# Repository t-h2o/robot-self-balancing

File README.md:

# robot-self-balancing

A self balancing robot made in [ETML](https://www.etml.ch/formations/automaticien.html)
was the final project of my CFC formation as automatician.

## PCB

The pcb has been designed with [KiCad](https://en.wikipedia.org/wiki/KiCad).
A very nice open-source software !

### Schematic

<p align="middle">
</p>

### PCB

<p align="middle">
</p>

## Mechanic

The mechanic design is made with [solid works](https://en.wikipedia.org/wiki/SolidWorks)

<p align="middle">
</p>

## Software

To compile the [code](software/main.ino),
we need the [IDE Arduino](https://www.arduino.cc/en/software)

## In-details documentation could be found here

- [The requirements](documentation/partlist)
- [full documentation](documentation/documentation_robot_self_balancing_all.pdf)

## Ressources

- [French channel](https://www.youtube.com/channel/UCe3v5cVACw-5BKQOcwUaM8w)
- An other [Self-Balancing Robot](https://www.instructables.com/Arduino-Self-Balancing-Robot-1/)

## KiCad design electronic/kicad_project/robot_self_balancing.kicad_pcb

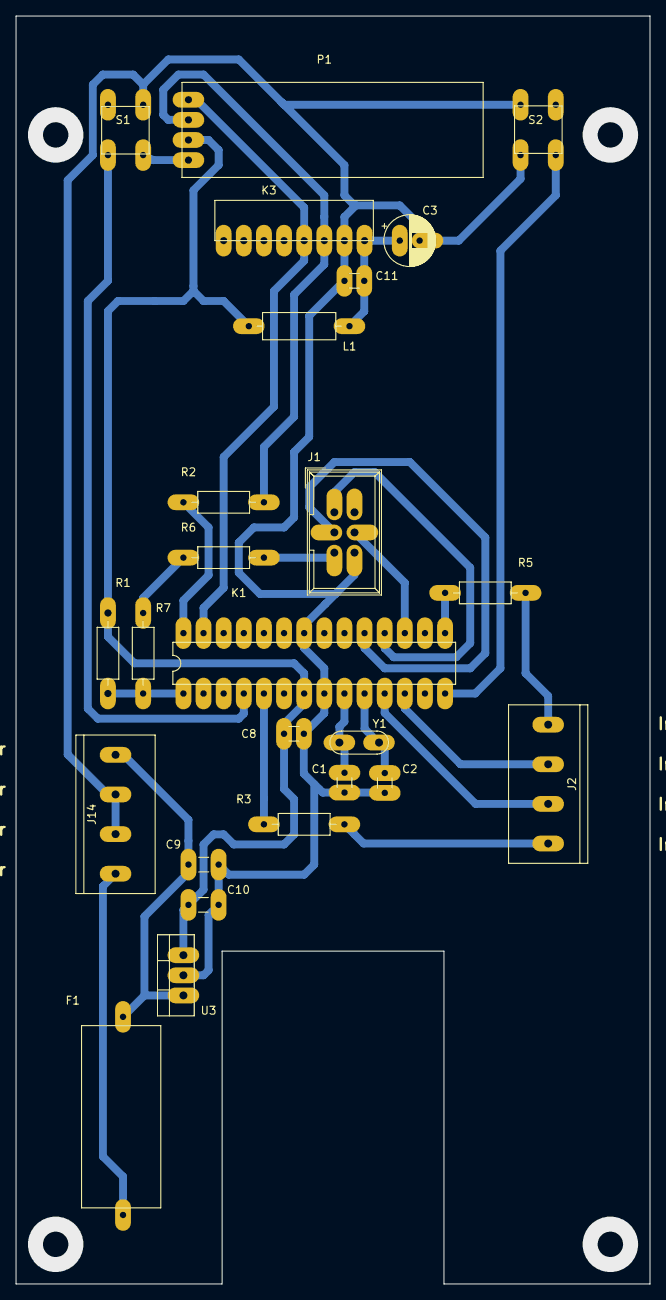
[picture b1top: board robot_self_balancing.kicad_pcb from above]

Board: 2 copper layers, 80.0 x 160.0 mm, 37 parts (0 on the bottom side), 23 nets.

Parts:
7V4: +7V4; TGL-NO_PRINT
BT1, BT2: LiPo 3V7; TGL-NO_PRINT
C1, C2: 22 pF; TGL-C_12pF
C3: 10μF; CP_Radial_D6.3mm_P2.50mm
C5, C6: 100nF; TGL-NO_PRINT
C8: 100 nF; TGL-C_12pF
C9, C10, C11: 100nF; TGL-C_12pF
F1: 630mA; TGL-Fuse
J1: Programmer; TGL_IDC-Header_2x03_P2.54mm_Vertical_1.2
J2: motor command; TGL-Bornier4Pins_mm
J11, J12: Accu LiPo; TGL-NO_PRINT
J13: Regulator charge; TGL-NO_PRINT
J14: Power bornier; TGL-Bornier4Pins_mm
K1: ATmega328P-PU; TGL-ATmega328P_PU
K3: MPU-6050; TGL-MPU_6050-perpendiculaire
L1: 1500nH; TGL_L
M1: Right; TGL-NO_PRINT
M2: Left; TGL-NO_PRINT
P1: OLED_Screen; TGL-OLED_Screen
R1: 10k; R_Axial_DIN0207_L6.3mm_D2.5mm_P10.16mm_Horizontal
R2, R3, R5, R6, R7: 0Ω; TGL_R
S1: Reset; TGL-Push_Button
S2: Set; TGL-Push_Button
S10: mainSwitch; TGL-NO_PRINT
T1: L298N; TGL-NO_PRINT
U3: 78M05CT; TO-220-3_Vertical
Y1: 20MHz; Resonator-2Pin_W7.0mm_H2.5mm

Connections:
20Mhz_1: C1.1, K1.9, Y1.1
20Mhz_2: C2.1, K1.10, Y1.2
+5V: C8.2, C10.1, K1.7, L1.2, P1.2, R1.1, U3.3
+7V4_500mA: C9.2, F1.1, J14.8, U3.1
D1-button_SET: K1.14, S2.2
D2-button_RESET: K1.4, S1.2
D3-left_motor_forward: K1.5, R3.2
D5-left_motor_backward: J2.7, K1.11
D6-right_motor_forward: J2.6, K1.12
D9-right_motor_backward: K1.15, R5.1
GND: C1.2, C2.2, C3.2, C8.1, C9.1, C10.2, C11.2, J1.6, J14.6, J14.7, K1.8, K1.22, K3.18, P1.1, S1.1, S2.1, U3.2
MISO: J1.1, K1.18
MOSI: J1.4, K1.17
unnamed: C3.1, C11.1, K3.13, L1.1
unnamed: F1.2, J14.5
unnamed: J1.5, R6.1
unnamed: J2.5, R5.2
unnamed: J2.8, R3.1
unnamed: R6.2, R7.1
RESET: K1.1, R1.2, R7.2
SCK: J1.3, K1.19
SCL: K1.28, K3.23, P1.3, R2.1, R2.2
SDA: K1.27, K3.24, P1.4

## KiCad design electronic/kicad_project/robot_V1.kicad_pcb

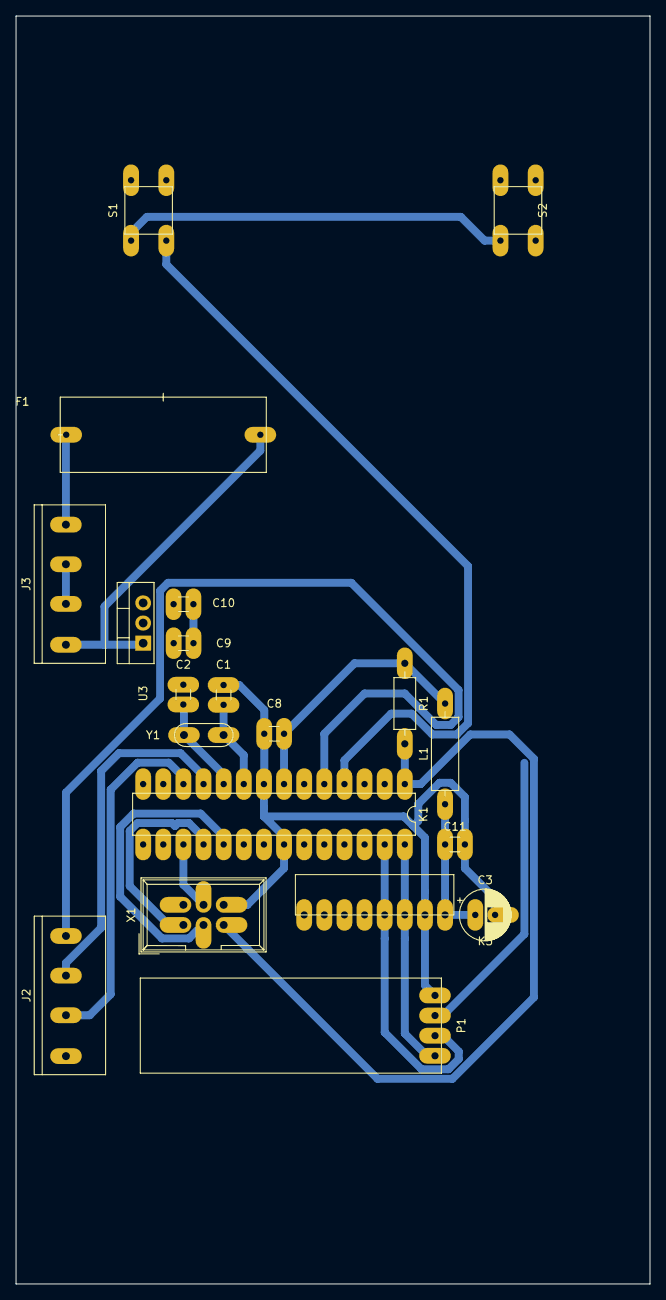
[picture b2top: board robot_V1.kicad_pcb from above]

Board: 2 copper layers, 80.0 x 160.0 mm, 28 parts (0 on the bottom side), 20 nets.

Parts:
7V4: +7V4; TGL-NO_PRINT
BT1, BT2: LiPo 3V7; TGL-NO_PRINT
C1, C2: 22 pF; TGL-C_12pF
C3: 10uF; CP_Radial_D6.3mm_P2.50mm
C5, C6: 1 mF; TGL-NO_PRINT
C8: 100 nF; TGL-C_12pF
C9, C10, C11: 100nF; TGL-C_12pF
F1: 500mA; TGL-Fuse
J2: Motor commands; TGL-Bornier4Pins_mm
J3: Power bornier; TGL-Bornier4Pins_mm
K1: ATmega328P-PU; TGL-ATmega328P_PU
K3: MPU-6050; TGL-MPU_6050-perpendiculaire
L1: 330_Ohms/100MHz/300nH; TGL_L
M1: Right; TGL-NO_PRINT
M2: Left; TGL-NO_PRINT
P1: OLED_Screen; TGL-OLED_Screen
R1: 10k; R_Axial_DIN0207_L6.3mm_D2.5mm_P10.16mm_Horizontal
S1: Reset; TGL-Push_Button
S2: Set; TGL-Push_Button
S3: Main switch power; TGL-NO_PRINT
U3: LM7805_TO220; TO-220-3_Vertical
X1: Conn 2x03; TGL_IDC-Header_2x03_P2.54mm_Vertical_1.2
Y1: Crystal 20 Mhz; Resonator-2Pin_W7.0mm_H2.5mm

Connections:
20Mhz_1: C1.1, K1.9, Y1.1
20Mhz_2: C2.1, K1.10, Y1.2
+5V: C8.2, C10.1, K1.7, L1.2, P1.2, R1.1, U3.3
+7V4_500mA: C9.2, F1.1, J3.8, U3.1
D1-button_SET: K1.3, S2.2
D2-button_RESET: K1.4, S1.2
D3-left_motor_forward: J2.8, K1.5
D5-left_motor_backward: J2.7, K1.11
D6-right_motor_forward: J2.6, K1.12
D9-right_motor_backward: J2.5, K1.15
GND: C1.2, C2.2, C3.2, C8.1, C9.1, C10.2, C11.2, K1.8, K1.22, K3.18, P1.1, S1.1, S2.1, U3.2, X1.6
MISO: K1.18, X1.1
MOSI: K1.17, X1.4
unnamed: C3.1, C11.1, K3.13, L1.1
unnamed: F1.2, J3.5
unnamed: J3.6, J3.7
RESET: K1.1, R1.2, X1.5
SCK: K1.19, X1.3
SCL: K1.28, K3.23, P1.4
SDA: K1.27, K3.24, P1.3

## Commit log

2021-09-15 copy files in git hub
2021-09-15 update read me
2021-09-15 mechanic plan pdf
2021-09-15 replace in correct place pdf files
2021-09-15 update read me
    Was
    --> was
2021-09-15 move main soft versions copy in a folder
2021-09-15 update readme - add links
    add link
2022-04-11 refresh the repository
